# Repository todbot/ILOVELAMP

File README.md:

# ILOVELAMP
Sketches and Ideas for I LOVE LAMP project

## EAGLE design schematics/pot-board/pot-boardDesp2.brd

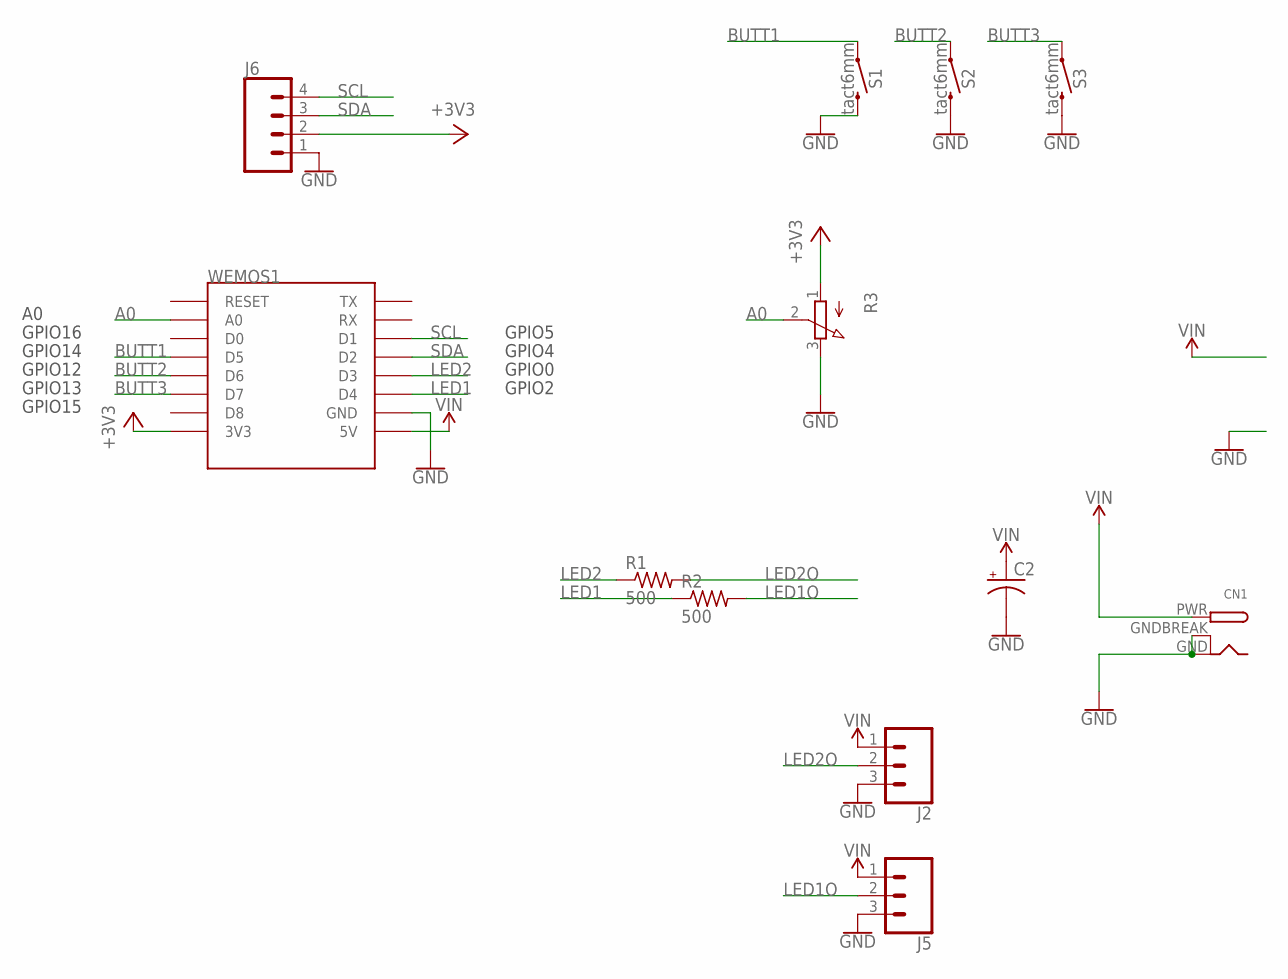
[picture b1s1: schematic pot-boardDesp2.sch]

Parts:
C2: CPOL-USE3.5-8; E3,5-8
CN1: DCBARRELPTH; DCJACK_2MM_PTH
J2, J5: CONN_03; 1X03
J6: CONN_04; 1X04
R1, R2: 500; R0805
R3: 3RP/1610N
S1, S2, S3: tact6mm; TACTILE_SWITCH_PTH_6.0MM
WEMOS1: WEMOS-D1-MINI

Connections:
+3V3: J6.2, R3.1 (A), WEMOS1.3V3
A0: R3.2 (S), WEMOS1.A0
BUTT1: S1.1, WEMOS1.D5
BUTT2: S2.1, WEMOS1.D6
BUTT3: S3.1, WEMOS1.D7
GND: C2.-, CN1.GND, CN1.GNDBREAK, J2.3, J5.3, J6.1, R3.3 (E), S1.3 (2), S2.3 (2), S3.3 (2), WEMOS1.GND
LED1: R2.1, WEMOS1.D4
LED1O: J5.2, R2.2
LED2: R1.1, WEMOS1.D3
LED2O: J2.2, R1.2
SCL: J6.4, WEMOS1.D1
SDA: J6.3, WEMOS1.D2
VIN: C2.+, CN1.PWR, J2.1, J5.1, WEMOS1.5V

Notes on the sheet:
GPIO2
GPIO0
GPIO4
GPIO5
GPIO13
GPIO15
GPIO12
GPIO14
GPIO16

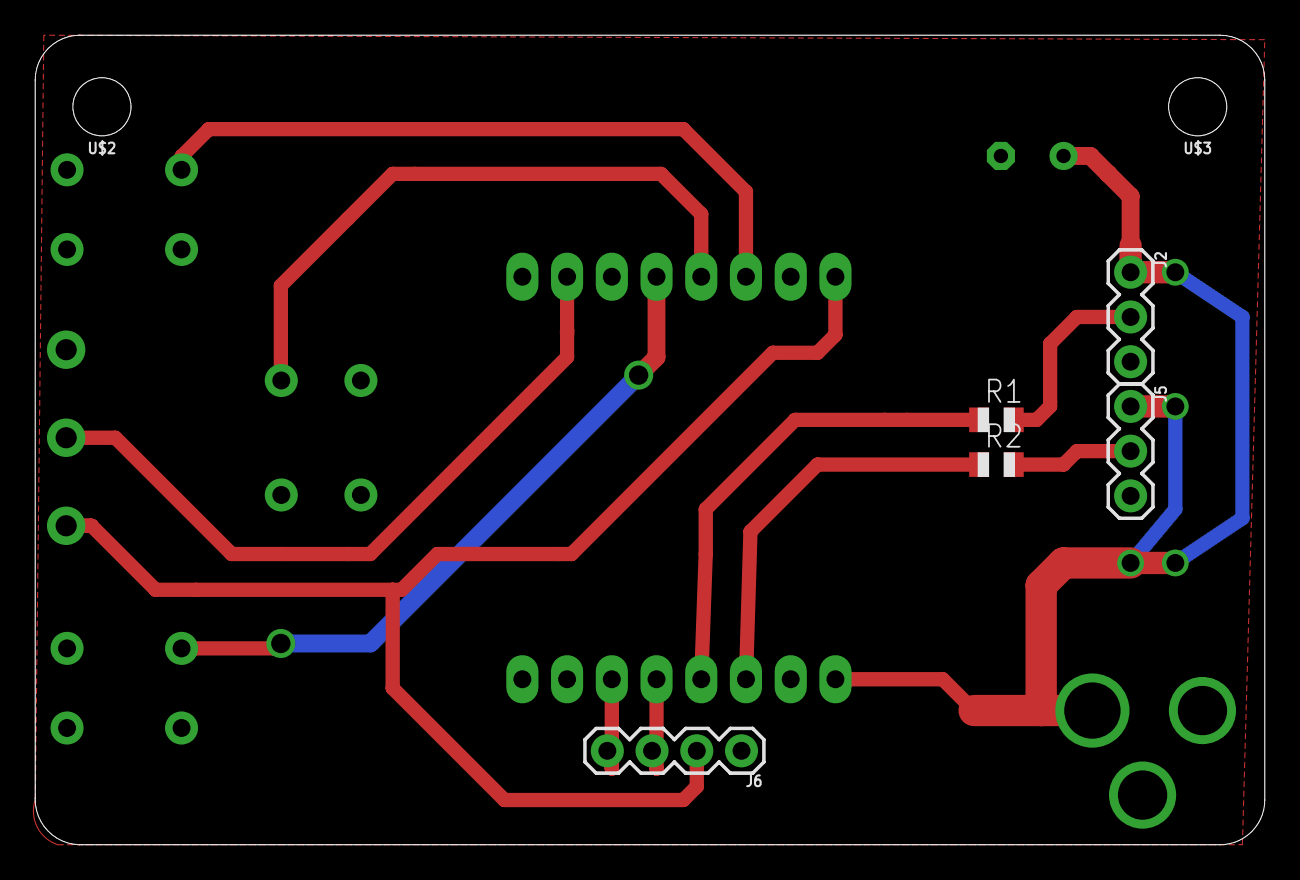
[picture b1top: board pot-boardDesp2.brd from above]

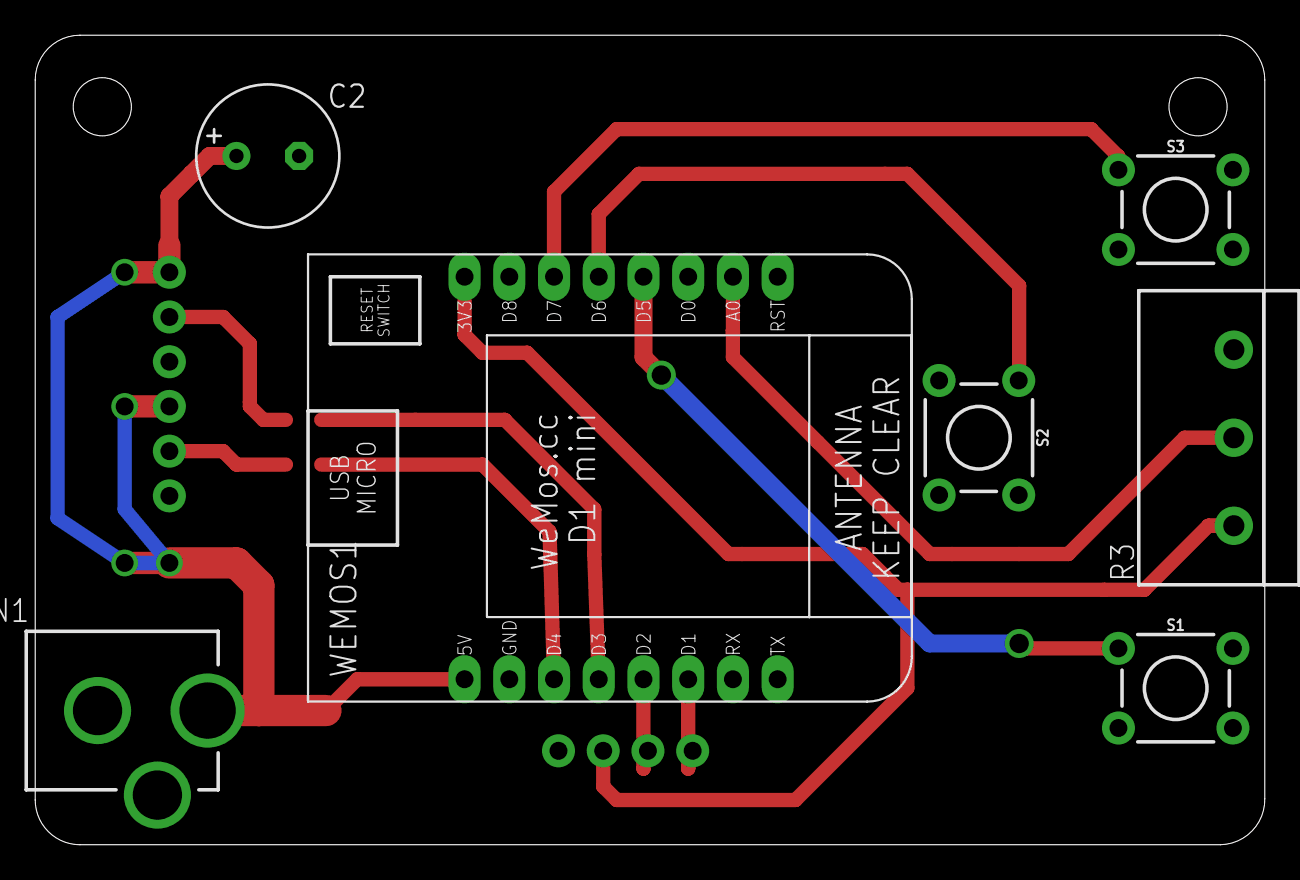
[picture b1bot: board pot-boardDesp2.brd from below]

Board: 2 copper layers, 69.8 x 46.0 mm, 14 parts (7 on the bottom side), 13 nets.

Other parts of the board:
U$2, U$3: STAND-OFF

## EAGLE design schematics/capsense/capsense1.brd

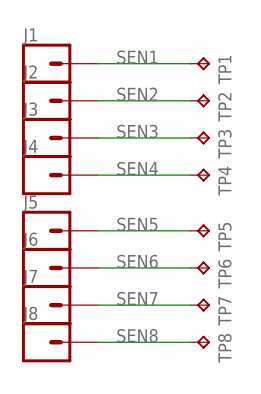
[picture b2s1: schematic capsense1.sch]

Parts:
J1, J2, J3, J4, J5, J6, J7, J8: CONN_01; 1X01
TP1, TP2, TP3, TP4, TP5, TP6, TP7, TP8: TPTP20R; TP20R

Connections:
SEN1: J1.1, TP1.TP
SEN2: J2.1, TP2.TP
SEN3: J3.1, TP3.TP
SEN4: J4.1, TP4.TP
SEN5: J5.1, TP5.TP
SEN6: J6.1, TP6.TP
SEN7: J7.1, TP7.TP
SEN8: J8.1, TP8.TP

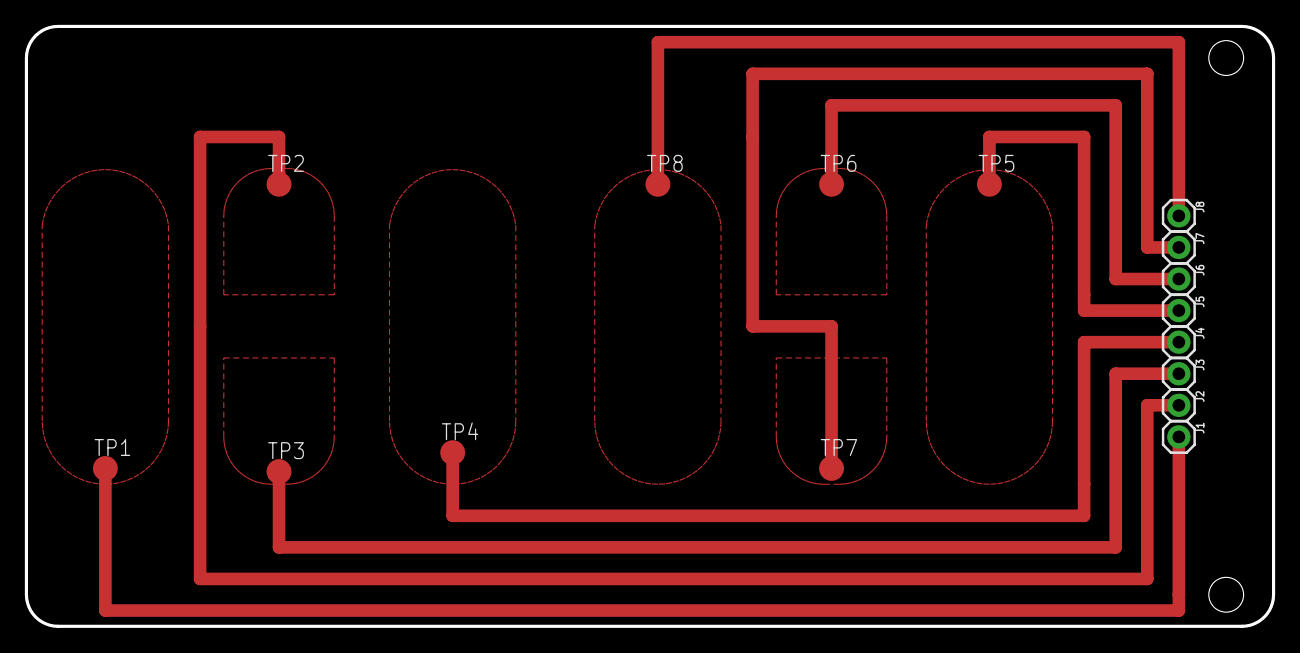
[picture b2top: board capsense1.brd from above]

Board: 2 copper layers, 100.3 x 48.3 mm, 16 parts (0 on the bottom side), 8 nets.

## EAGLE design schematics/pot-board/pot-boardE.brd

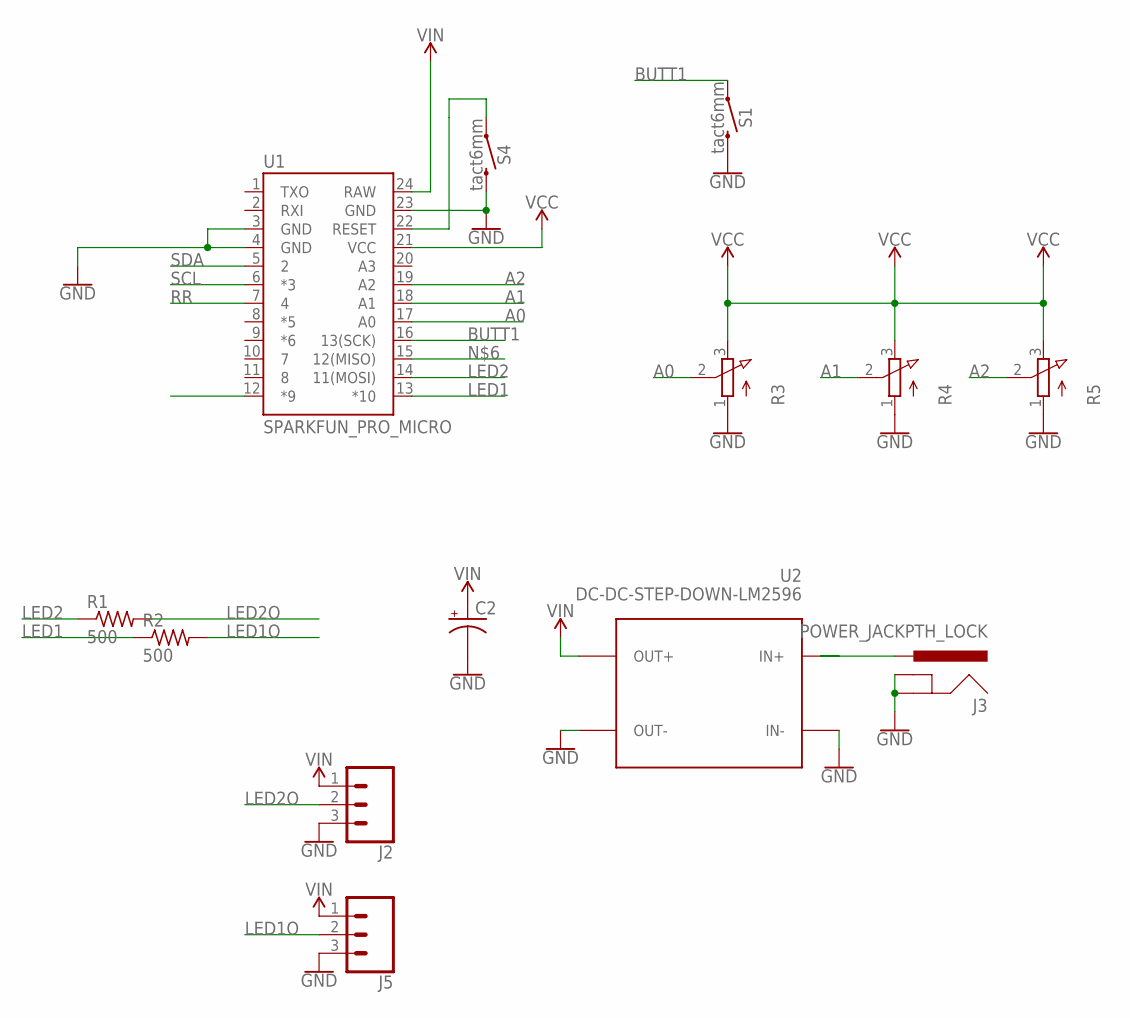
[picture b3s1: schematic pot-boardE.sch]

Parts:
C2: CPOL-USE3.5-8; E3,5-8
J2, J5: CONN_03; 1X03
J3: POWER_JACKPTH_LOCK; POWER_JACK_PTH_LOCK
R1, R2: 500; R0805
R3, R4, R5: 3RP/1610N
S1, S4: tact6mm; TACTILE_SWITCH_PTH_6.0MM
U1: SPARKFUN_PRO_MICRO
U2: DC-DC-STEP-DOWN-LM2596

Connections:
A0: R3.2 (S), U1.17 (A0)
A1: R4.2 (S), U1.18 (A1)
A2: R5.2 (S), U1.19 (A2)
BUTT1: S1.1, U1.16 (13(SCK))
GND: C2.-, J2.3, J3.GND, J3.GNDBREAK, J5.3, R3.1 (A), R4.1 (A), R5.1 (A), S1.3 (2), S4.3 (2), U1.3 (GND), U1.4 (GND), U1.23 (GND), U2.IN-, U2.OUT-
LED1: R2.1, U1.13 (*10)
LED1O: J5.2, R2.2
LED2: R1.1, U1.14 (11(MOSI))
LED2O: J2.2, R1.2
unnamed: J3.PWR, U2.IN+
RESET: S4.1, U1.22 (RESET)
RR: U1.7 (4)
SCL: U1.6 (*3)
SDA: U1.5 (2)
VCC: R3.3 (E), R4.3 (E), R5.3 (E), U1.21 (VCC)
VIN: C2.+, J2.1, J5.1, U1.24 (RAW), U2.OUT+

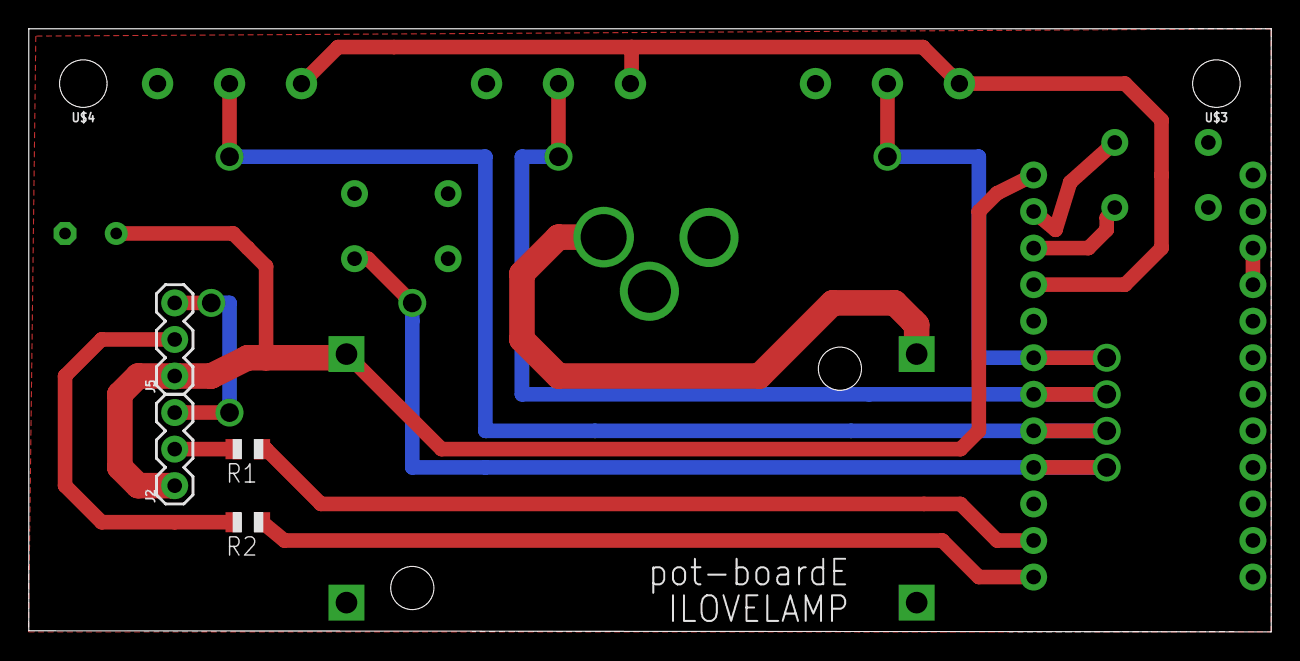
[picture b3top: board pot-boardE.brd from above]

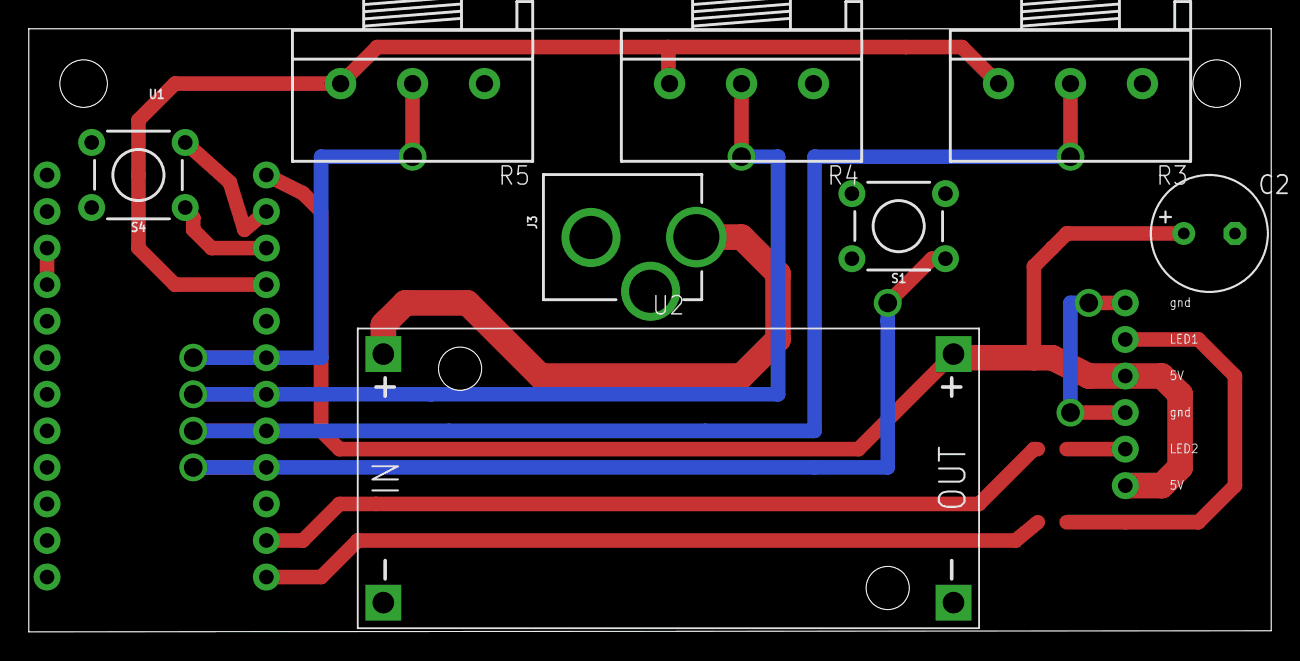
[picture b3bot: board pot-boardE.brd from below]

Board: 2 copper layers, 86.3 x 41.9 mm, 15 parts (9 on the bottom side), 13 nets.

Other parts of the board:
U$3, U$4: STAND-OFF

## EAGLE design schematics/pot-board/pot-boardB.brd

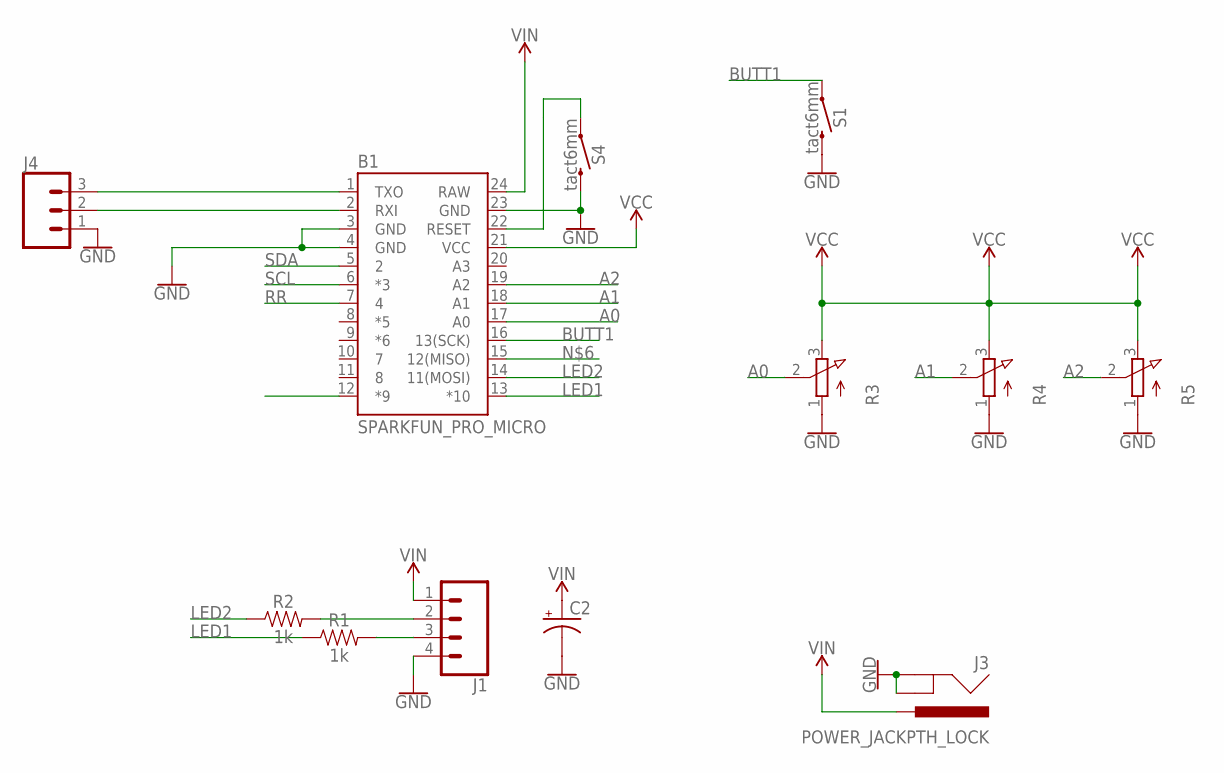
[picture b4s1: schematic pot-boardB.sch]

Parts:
B1: SPARKFUN_PRO_MICRO
C2: CPOL-USE3.5-8; E3,5-8
J1: CONN_04; 1X04
J3: POWER_JACKPTH_LOCK; POWER_JACK_PTH_LOCK
J4: CONN_03; 1X03
R1, R2: 1k; AXIAL-0.3
R3, R4, R5: 3RP/1610N
S1, S4: tact6mm; TACTILE_SWITCH_PTH_6.0MM

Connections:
A0: B1.17 (A0), R3.2 (S)
A1: B1.18 (A1), R4.2 (S)
A2: B1.19 (A2), R5.2 (S)
BUTT1: B1.16 (13(SCK)), S1.1
GND: B1.3 (GND), B1.4 (GND), B1.23 (GND), C2.-, J1.4, J3.GND, J3.GNDBREAK, J4.1, R3.1 (A), R4.1 (A), R5.1 (A), S1.3 (2), S4.3 (2)
LED1: B1.13 (*10), R1.P$1 (1)
LED2: B1.14 (11(MOSI)), R2.P$1 (1)
unnamed: J1.3, R1.P$2 (2)
unnamed: J1.2, R2.P$2 (2)
unnamed: B1.2 (RXI), J4.2
unnamed: B1.1 (TXO), J4.3
RESET: B1.22 (RESET), S4.1
RR: B1.7 (4)
SCL: B1.6 (*3)
SDA: B1.5 (2)
VCC: B1.21 (VCC), R3.3 (E), R4.3 (E), R5.3 (E)
VIN: B1.24 (RAW), C2.+, J1.1, J3.PWR

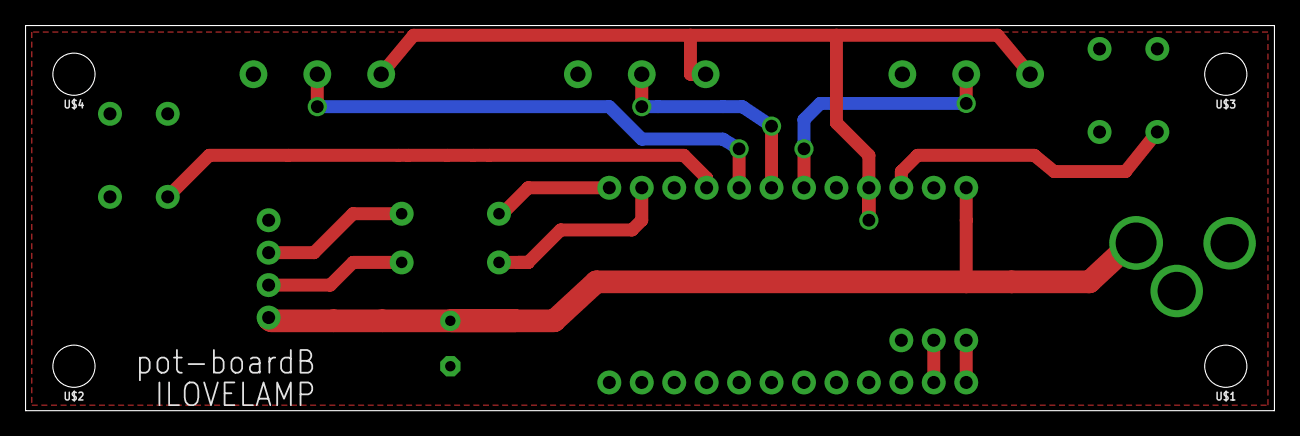
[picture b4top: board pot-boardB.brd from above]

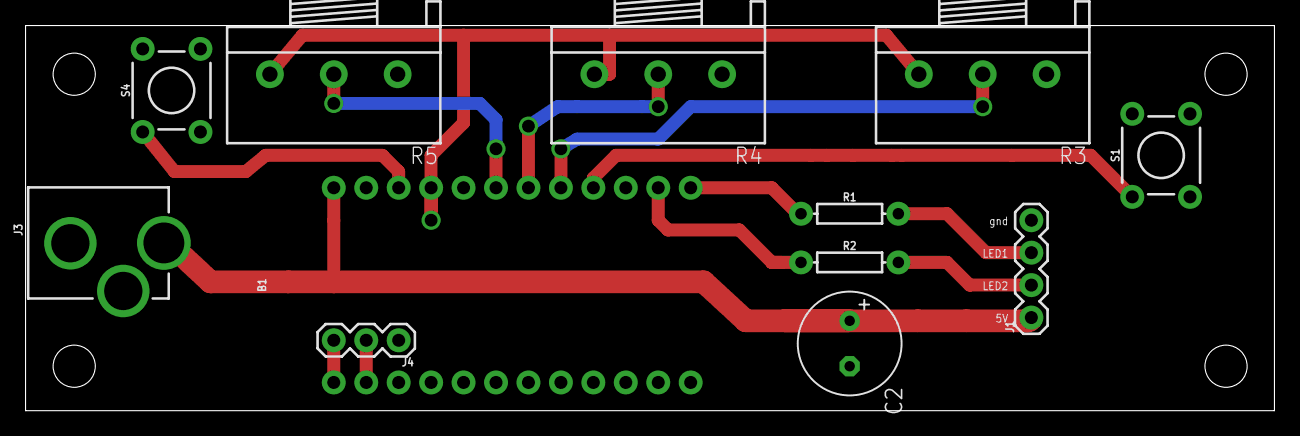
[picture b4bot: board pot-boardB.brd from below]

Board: 2 copper layers, 97.8 x 30.2 mm, 16 parts (12 on the bottom side), 14 nets.

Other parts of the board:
U$1, U$2, U$3, U$4: STAND-OFF

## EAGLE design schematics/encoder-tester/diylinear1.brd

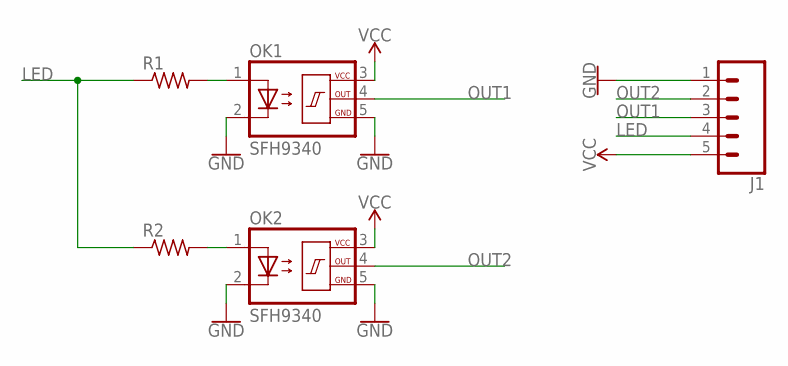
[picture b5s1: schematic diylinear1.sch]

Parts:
J1: CONN_05; 1X05
OK1, OK2: SFH9340
R1, R2: R-US_0204/5; 0204/5

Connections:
GND: J1.1, OK1.2 (C), OK1.5 (GND), OK2.2 (C), OK2.5 (GND)
LED: J1.4, R1.1, R2.1
unnamed: OK1.1 (A), R1.2
unnamed: OK2.1 (A), R2.2
OUT1: J1.3, OK1.4 (OUT)
OUT2: J1.2, OK2.4 (OUT)
VCC: J1.5, OK1.3 (VCC), OK2.3 (VCC)

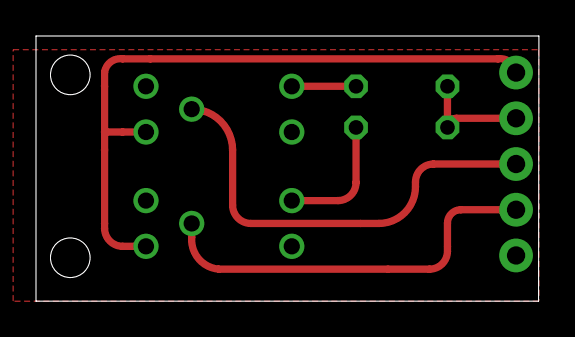
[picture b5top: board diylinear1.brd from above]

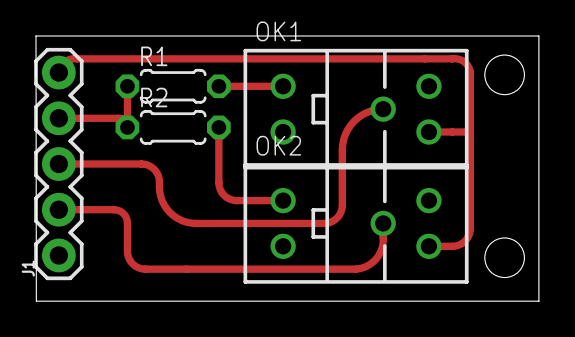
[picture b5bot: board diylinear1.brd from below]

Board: 2 copper layers, 27.9 x 14.7 mm, 5 parts (5 on the bottom side), 7 nets.

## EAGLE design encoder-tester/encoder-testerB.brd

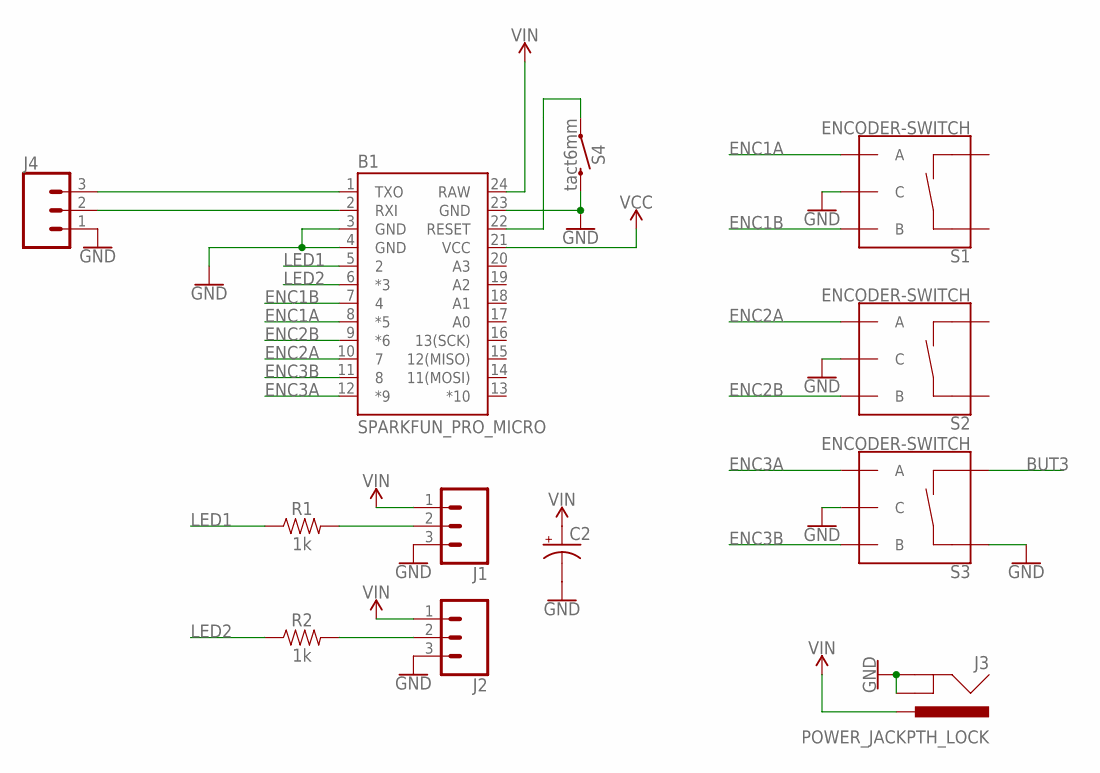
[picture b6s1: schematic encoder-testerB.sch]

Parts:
B1: SPARKFUN_PRO_MICRO
C2: CPOL-USE3.5-8; E3,5-8
J1, J2, J4: CONN_03; 1X03
J3: POWER_JACKPTH_LOCK; POWER_JACK_PTH_LOCK
R1, R2: 1k; AXIAL-0.3
S1, S2, S3: ENCODER-SWITCH; ROTARY_ENC_PLAIN
S4: tact6mm; TACTILE_SWITCH_PTH_6.0MM

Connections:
BUT3: S3.SW-
ENC1A: B1.8 (*5), S1.A
ENC1B: B1.7 (4), S1.B
ENC2A: B1.10 (7), S2.A
ENC2B: B1.9 (*6), S2.B
ENC3A: B1.12 (*9), S3.A
ENC3B: B1.11 (8), S3.B
GND: B1.3 (GND), B1.4 (GND), B1.23 (GND), C2.-, J1.3, J2.3, J3.GND, J3.GNDBREAK, J4.1, S1.C, S2.C, S3.C, S3.SW+, S4.3 (2)
LED1: B1.5 (2), R1.P$1 (1)
LED2: B1.6 (*3), R2.P$1 (1)
unnamed: J1.2, R1.P$2 (2)
unnamed: J2.2, R2.P$2 (2)
unnamed: B1.2 (RXI), J4.2
unnamed: B1.1 (TXO), J4.3
RESET: B1.22 (RESET), S4.1
VCC: B1.21 (VCC)
VIN: B1.24 (RAW), C2.+, J1.1, J2.1, J3.PWR

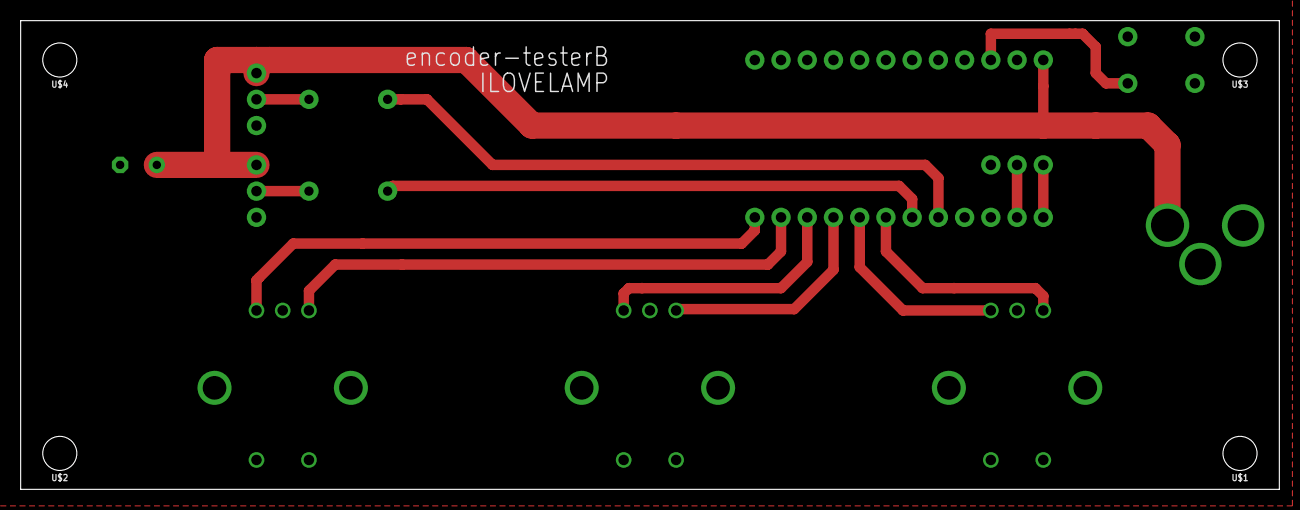
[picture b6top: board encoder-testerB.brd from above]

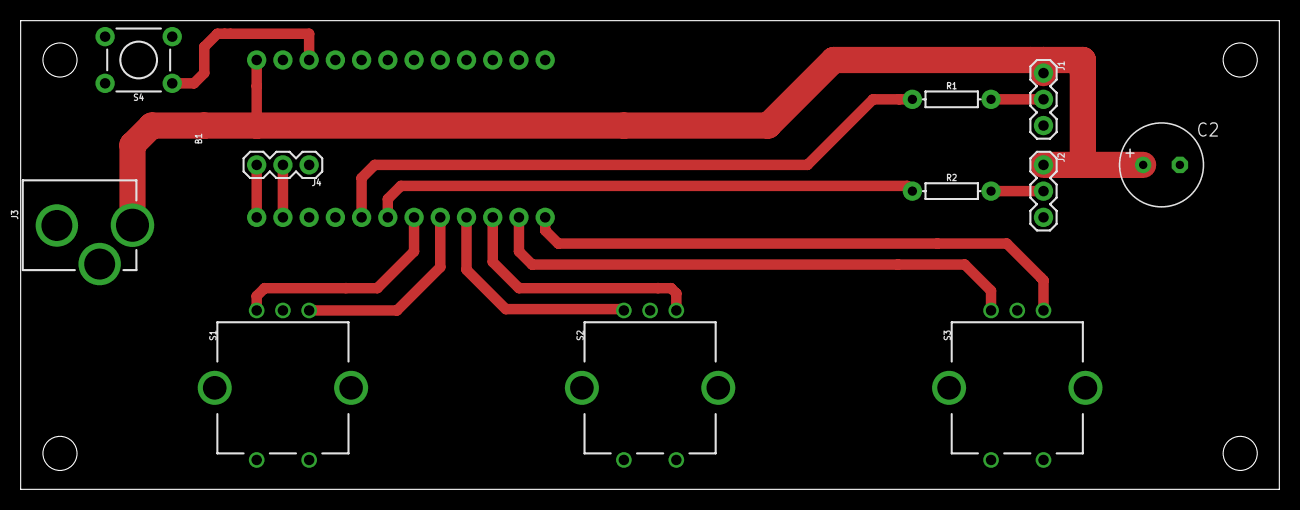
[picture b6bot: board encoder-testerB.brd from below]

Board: 2 copper layers, 121.9 x 45.4 mm, 16 parts (12 on the bottom side), 15 nets.

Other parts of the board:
U$1, U$2, U$3, U$4: STAND-OFF

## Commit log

2017-03-06 added encoder test
2017-03-08 board fixups
2017-03-08 last changes to this initial sketch
2017-03-08 next set of tests
2017-03-09 small fixes to sketches
2017-03-16 added diy linear encoder test board
2017-03-16 added second encoder test sketch
2017-03-18 reorg
2017-03-21 new sketch
2017-03-21 nice lampmode for archMetal1
2017-03-29 added diy linear encoder tests
2017-03-30 added sketches for lamps
2017-04-04 small fixes
2017-04-05 added button to helixMetal1
2017-04-25 added pot-boards
2017-04-26 added variations up to woodArc1 using pot-boardE
2017-05-13 added esp pot boards
2017-05-13 added capsense board
2017-05-17 added woodArc3 sketch
2017-05-18 added some modes to woodArc3
2017-05-19 added lasercutWoodArc1
2017-05-23 weird version
2017-06-16 added new boards
2017-06-16 added sketches

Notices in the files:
parts and their libraries:
SparkFun-Boards: Licensing: Creative Commons ShareAlike 4.0 International - https://creativecommons.org/licenses/by-sa/4.0
diy-modules: Released under the Creative Commons Attribution 4.0 International License: http://creativecommons.org/licenses/by/4.0
